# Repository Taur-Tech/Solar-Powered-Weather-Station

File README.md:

# Solar-Powered-Weather-Station
Design files for a solar powered weather station.

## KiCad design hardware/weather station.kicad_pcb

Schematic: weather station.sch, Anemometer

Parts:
C1, C6, C13: 220u; CP_Elec_8x10.5
C2, C5, C8, C9, C10, C11, C12: .1u; C_0805_2012Metric_Pad1.15x1.40mm_HandSolder
C3, C4, C7: 1u; C_0805_2012Metric_Pad1.15x1.40mm_HandSolder
D1, D2, D4, D5: D; D_SMB_Handsoldering
D3: LED; LED_1206_3216Metric_Pad1.42x1.75mm_HandSolder
J1: Conn_01x05; PinHeader_1x05_P2.54mm_Vertical
J2: DIG_EXP; PinHeader_1x06_P2.54mm_Vertical
J3: ICSP; PinHeader_1x05_P2.54mm_Vertical
J4: BAT.; TerminalBlock_4Ucon_1x02_P3.50mm_Horizontal
J5: EXP0; PinHeader_1x04_P2.54mm_Vertical
J6: EXP1; PinHeader_1x04_P2.54mm_Vertical
J7: Wind; PinHeader_1x05_P2.54mm_Vertical
J8: Conn_01x08; PinHeader_1x08_P2.54mm_Vertical
J9: HMC5883L; PinHeader_1x05_P2.54mm_Vertical
J10: Pressure; PinHeader_1x06_P2.54mm_Vertical
J11: Conn_01x04; PinHeader_1x04_P2.54mm_Vertical
J12: Conn_02x07_Odd_Even; PinSocket_2x07_P2.00mm_Vertical
R1: 680R; R_0805_2012Metric_Pad1.15x1.40mm_HandSolder
R2: 10K; R_0805_2012Metric_Pad1.15x1.40mm_HandSolder
R3, R5: 4k7; R_0805_2012Metric_Pad1.15x1.40mm_HandSolder
R4, R8, R9: 100R; R_0805_2012Metric_Pad1.15x1.40mm_HandSolder
R6, R10: 100k; R_0805_2012Metric_Pad1.15x1.40mm_HandSolder
R7: 10k; R_0805_2012Metric_Pad1.15x1.40mm_HandSolder
R11, R12: 1M; R_0805_2012Metric_Pad1.15x1.40mm_HandSolder
R13, R14, R15, R16, R17: 0R; R_0805_2012Metric_Pad1.15x1.40mm_HandSolder
U1: 18650_CHARGER; TP4056
U2: dsPIC30F4011; QFN-44-1EP_8x8mm_P0.65mm_EP6.6x6.6mm
U3: DC-DC(5V); DM06
U4: TLE2426xD; SOIC-8_3.9x4.9mm_P1.27mm
U5, U6: LM2904; TSSOP-8_4.4x3mm_P0.65mm
U7: TLV70033_SOT23-5; SOT-23-5

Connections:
+5V: C5.1, C6.1, C8.1, C9.1, C10.1, C11.1, J2.1, J3.2, J5.1, J6.1, J7.5, R2.2, R3.1, R5.1, R15.2, R16.2, R17.2, U2.7, U2.8, U2.17, U2.28, U2.29, U2.40, U3.4, U4.3, U5.8, U6.8
+BATT: D5.2, J4.1, U1.4, U7.1 (IN)
AN0: R8.2, U2.22
AN1: R9.2, U2.23
CTRL0: R13.2, U2.14
CTRL1: R14.2, U2.12
GND: C1.2, C2.2, C3.2, C4.2, C5.2, C6.2, C7.2, C8.2, C9.2, C10.2, C11.2, C12.2, C13.2, D3.1, J1.4, J1.5, J2.6, J3.3, J4.2, J5.4, J6.4, J7.3, J8.5, J9.2, J10.6, J11.3, J12.1, R7.2, R11.2, R12.2, U1.2, U1.3, U2.6, U2.16, U2.30, U2.31, U2.39, U3.2, U3.3, U4.2, U5.4, U6.4, U7.2 (GND)
LED: R1.2, U2.35
unnamed: C3.1, D4.1, D5.1, U3.1
unnamed: C7.1, U4.8
unnamed: C12.1, C13.1, J8.4, J12.2, U7.5 (OUT)
unnamed: D1.2, J1.1
unnamed: D2.2, J1.2
unnamed: D3.2, R1.1
unnamed: J2.2, U2.42
unnamed: J2.3, U2.37
unnamed: J2.4, U2.41
unnamed: J2.5, U2.38
unnamed: J3.1, R2.1, U2.18
unnamed: J5.2, R11.1, U6.3
unnamed: J5.3, R13.1
unnamed: J6.2, R12.1, U6.5
unnamed: J6.3, R14.1
unnamed: J7.4, R10.1, U5.5
unnamed: J9.1, R15.1
unnamed: J10.1, R16.1
unnamed: J11.4, R17.1
unnamed: R4.1, U5.1, U5.2
unnamed: R4.2, U2.21
unnamed: R6.2, R7.1, U5.3
unnamed: R8.1, U6.1, U6.2
unnamed: R9.1, U6.6, U6.7
PGC: J3.5, J9.4, J10.3, J11.1, R3.2, U2.1
PGD: J3.4, J9.3, J10.2, J11.2, R5.2, U2.44
SOLAR_PANEL: C1.1, C2.1, D1.1, D2.1, D4.2, R6.1, U1.1
VGND: C4.1, J7.1, R10.2, U2.19, U2.20, U4.1
WIFI_BOOT: J8.3, J12.8, U2.43
WIFI_EN: U2.15, U7.3 (EN)
WIFI_READY: J8.1, J12.9, U2.4
WIFI_RESET: J8.6, J12.7, U2.5
WIFI_RX: J8.7, J12.3, U2.3
WIFI_TX: J8.8, J12.4, U2.2
WIND: U2.27, U5.6, U5.7

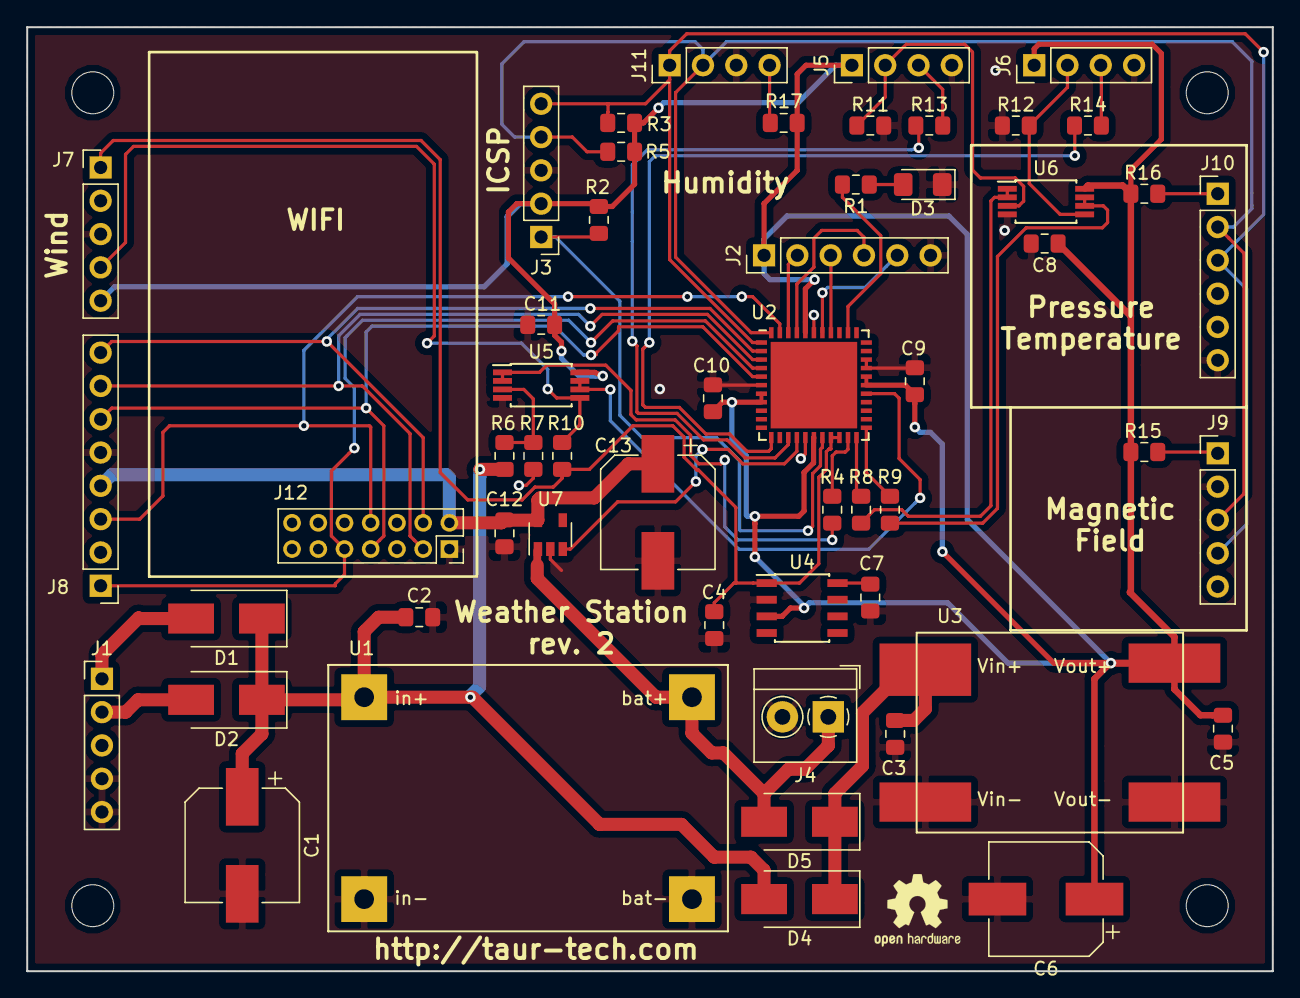
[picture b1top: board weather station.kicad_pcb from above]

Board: 2 copper layers, 95.0 x 72.0 mm, 54 parts (0 on the bottom side), 43 nets.

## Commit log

2016-10-10 Added HMC5883L, BMP085, I2C and UART functions
2016-10-10 fixups
2016-12-21 added basic anemometer
2016-12-23 Anemometer: modify input R for instr amp
2017-01-03 Add Si7021 humidity sensor driver
2017-01-03 add calibration parameters for anemometer
2017-02-25 define adc resolution
2017-10-09 first run on Wifi ok
2018-09-27 add solar panel output monitoring
2018-10-02 WIP: adding HW resources
2018-10-03 pcb layout complete
